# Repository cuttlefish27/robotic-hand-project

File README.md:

# Robotic Hand Project

An ongoing personal robotics project exploring robotic dexterity, motion control, and tactile sensing. This project includes a tendon-driven robotic hand, control software, and a custom magnetic tactile sensor that are all under development.

The long-term goal is to explore how mechanical design, control systems, and sensory feedback can work together to enable more capable robotic manipulation.

## Repository Structure

```text
robotic-hand-project/
├── hand-controller/            # Hand control software
    ├── mcu-firmware/               # MCU code
    ├── software/                   # Blender script & blender-mcu bridge
    └── hand_telemetry_rig.blend
├── sensor-dev/                 # Tactile sensor development
    ├── hardware/                   # PCB schematics & layout
    ├── software/                   # Sensor validation & data display
    └── firmware/                   # MCU firmware
├── .gitignore
├── LICENSE
└── README.md
```

### [`hand-controller/`](/hand-controller/README.md) — Robotic Hand Control

Contains the software for controlling the robotic hand from a computer and microcontroller.

The control system connects virtual hand poses to the physical robotic hand, using computer-side processing and embedded control to translate target movements into actuator commands.

The project explores:
- Blender-based hand pose control and visualization.
- Joint-angle calculations and kinematics.
- Communication between computer-side software and the microcontroller.
- Servo-based actuation of the robotic hand.

### [`sensor-dev/`](/sensor-dev/README.md) — Soft Magnetic Tactile Sensor

Contains the hardware designs and software for developing a compact tactile sensor for the robotic hand.

The sensor uses magnetic field measurements to investigate how applied forces can be measured at the fingertip. The design combines magnetic sensing components with custom PCB electronics.

Development focuses on:
- Sensor circuit and PCB design.
- Hall-effect sensor readout and data collection.
- Characterizing sensor response to applied forces.
- Developing calibration methods for force measurement.
- Exploring tactile sensing for future robotic manipulation.

The sensor is a work in progress, with measurement consistency, calibration, and integration remaining areas of development.

## System Overview

The project has two complementary systems:

**Hand control:** A computer generates or processes target poses, calculates the corresponding joint commands, and communicates with the microcontroller. The microcontroller then controls the hand's servos.

**Tactile sensing:** A custom magnetic sensor measures changes in magnetic fields associated with applied contact forces. The sensor electronics and software are being developed to make these measurements useful for robotic applications.

Together, these systems provide a foundation for exploring the relationship between robotic motion and tactile perception.

## Hardware

The project uses or explores the following hardware:

| Component | Purpose |
|---|---|
| ESP32 | Microcontroller for hand control |
| PCA9685 | Multi-channel servo control |
| Servo motors | Robotic hand actuation |
| Hall-effect sensors | Magnetic field measurements for tactile sensing |
| Custom PCBs | Tactile sensor electronics |

Hardware configurations will change as the design evolves.

## Software and Tools

- **Python** — Computer-side control, kinematics, serial communication, and sensor data processing.
- **Blender** — Hand pose control and 3D visualization.
- **C/C++** — Microcontroller firmware.
- **PlatformIO / Arduino framework** — Embedded development.
- **Fusion 360** — Mechanical CAD and hardware design.
- **KiCAD** — Circuit design and PCB layout.

## Development Goals

Current and planned areas of development include:

- Improving the robotic hand's mechanical design and range of motion.
- Developing responsive and reliable computer-to-microcontroller control.
- Designing a compact magnetic tactile sensor suitable for a robotic fingertip.
- Calibrating sensor measurements against known applied forces.
- Exploring how tactile feedback could support future VLA-based closed-loop control and robotic manipulation.

## Project Status

This is an active work-in-progress project. The hand controller, mechanical design, and tactile sensor are developed iteratively. Sensor integration and improvements to the broader mechanical design remain ongoing development goals.

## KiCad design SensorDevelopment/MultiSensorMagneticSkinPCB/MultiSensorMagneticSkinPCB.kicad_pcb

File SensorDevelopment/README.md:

This folder contains my work for designing a custom magnetic sensor for my robotic hand.

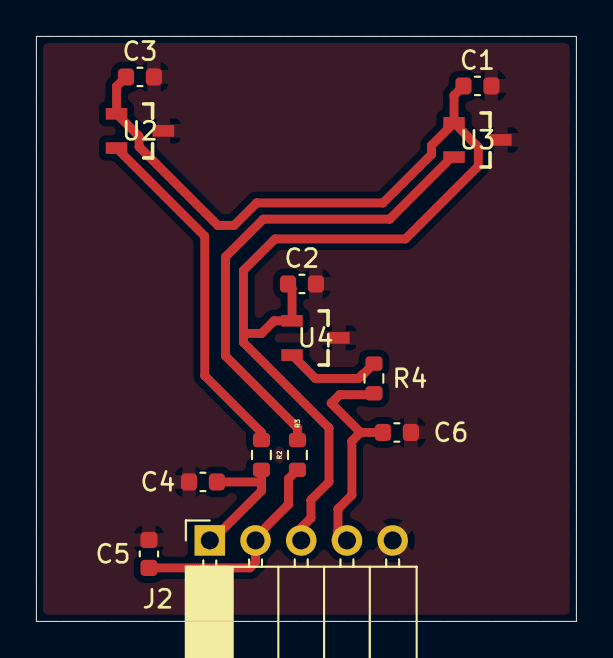
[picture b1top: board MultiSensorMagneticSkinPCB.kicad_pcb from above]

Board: 2 copper layers, 30.0 x 32.5 mm, 13 parts (0 on the bottom side), 8 nets.

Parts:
C1, C2, C3, C4, C5, C6: 0.1 microFarad; C_0603_1608Metric
J2: Conn_01x05; PinSocket_1x05_P2.54mm_Horizontal
R2, R3, R4: 10k Ohm; R_0603_1608Metric
U2, U3, U4: DRV5056A4EDBZRQ1; DBZ0003A_M

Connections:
GND: C1.2, C2.2, C3.2, C4.2, C5.2, C6.2, J2.5, U2.3 (GND), U3.3 (GND), U4.3 (GND)
unnamed: C4.1, J2.1, R2.2
unnamed: C5.1, J2.2, R3.2
unnamed: C6.1, J2.4, R4.2
unnamed: R2.1, U2.2 (OUT)
unnamed: R3.1, U3.2 (OUT)
unnamed: R4.1, U4.2 (OUT)
VCC: C1.1, C2.1, C3.1, J2.3, U2.1 (VCC), U3.1 (VCC), U4.1 (VCC)
